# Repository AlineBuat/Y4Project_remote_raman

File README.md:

# Y4Project_remote_raman
Final Year MEng Biomedical Engineering Individual Project code

Created by Aline BUAT, 2021-2022

Project title "Detecting Bioweapons with Standoff Raman Spectroscopy"

These are code and files used during the project and used to generate the figures in the Final Report.

This repository contains the following folders:
- the code used to analyse data
- Arduino Control: arduino programs used to send positional data to the DACs, used to control Galvo Mirrors. Arduino programs to read data from a Quadrant photodiode, and translate it into positional information. program to Send and receive packets using NRF24L01 transceiver modules on Arduino Nano (transmitter) and Arduino Due (Receiver).
- EagleShield: Arduino Shield layout (schematic, board, project files) to control 2 galvo mirrors
- Raman: spectral data (.csv)  in folders. MATLAB programs to analyse the spectral data (plotRaman_20220601.m). requires the "BEADS" MATLAB package to run.
- BeamQuality: analyse images containing laser spots as imaged by a camera evaluated along a distance around the focal point, to find the spot size. Finally, plot spot size vs distance around the focal point to find M squared quality of the beam.

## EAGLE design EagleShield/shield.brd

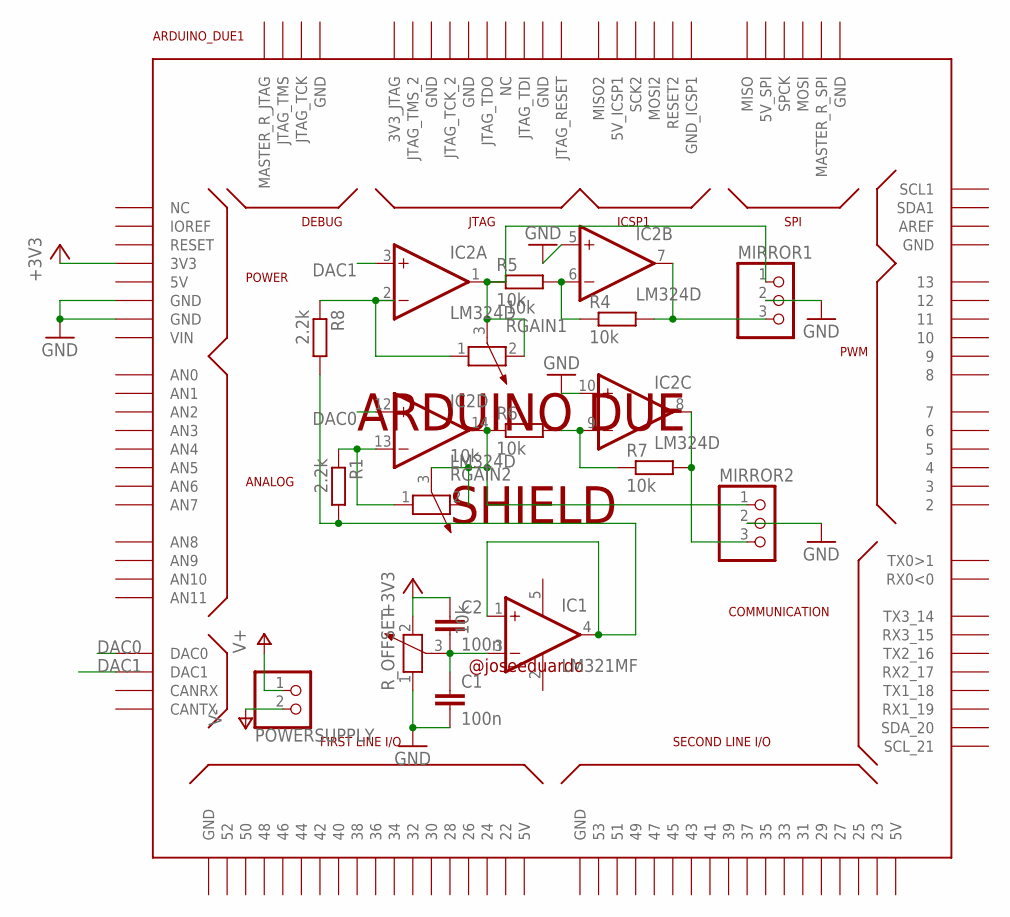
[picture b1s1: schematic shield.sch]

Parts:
ARDUINO_DUE1: ARDUINO_DUE_SHIELD
C1, C2: 100n; C0201
IC1: LM321MF; SOT23-5
IC2: LM324D; SO14
MIRROR1, MIRROR2: PINHD-1X3; 1X03
POWERSUPPLY: PINHD-1X2; 1X02
R1, R8: 2.2k; 0207/10
R4, R5, R6, R7: 10k; 0207/10
RGAIN1, RGAIN2: 10k; PT-10
R_OFFSET: 10k; PT-10

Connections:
+3V3: ARDUINO_DUE1.3V3, C2.1, R_OFFSET.2
DAC0: ARDUINO_DUE1.DAC0, IC2.12 (+IN)
DAC1: ARDUINO_DUE1.DAC1, IC2.3 (+IN)
GND: ARDUINO_DUE1.GND, ARDUINO_DUE1.GND_1 (GND), C1.2, IC2.5 (+IN), IC2.10 (+IN), MIRROR1.2, MIRROR2.2, R_OFFSET.1
unnamed: IC2.6 (-IN), R4.1, R5.2
unnamed: IC1.1 (+IN), IC1.4 (OUT), R1.2, R8.2
unnamed: IC2.9 (-IN), R6.2, R7.1
unnamed: IC2.1 (OUT), MIRROR1.1, R5.1, RGAIN1.2, RGAIN1.3
unnamed: IC2.2 (-IN), R8.1, RGAIN1.1
unnamed: IC2.14 (OUT), MIRROR2.1, R6.1, RGAIN2.2, RGAIN2.3
unnamed: IC2.8 (OUT), MIRROR2.3, R7.2
unnamed: IC2.13 (-IN), R1.1, RGAIN2.1
unnamed: IC2.7 (OUT), MIRROR1.3, R4.2
unnamed: C1.1, C2.2, IC1.3 (-IN), R_OFFSET.3
V+: IC1.5 (V+), IC2.4 (V+), POWERSUPPLY.1
V-: IC1.2 (V-), IC2.11 (V-), POWERSUPPLY.2

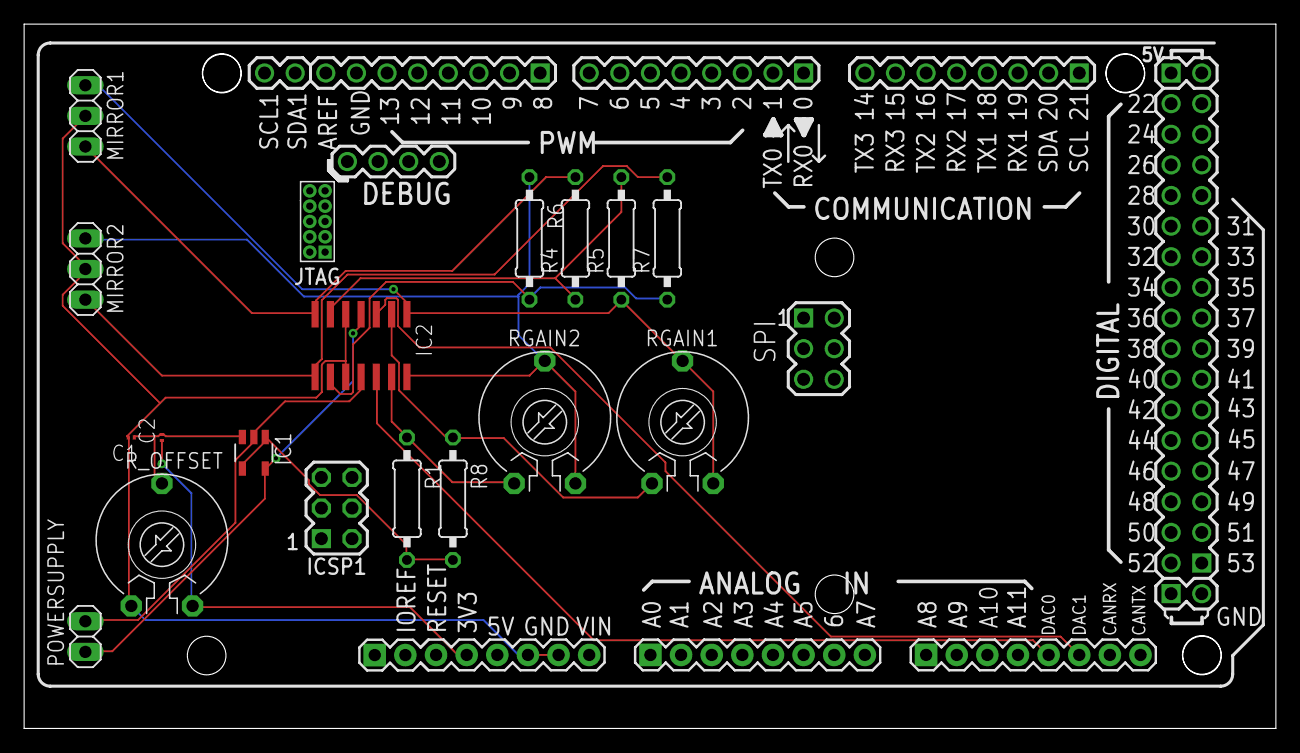
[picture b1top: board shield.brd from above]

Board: 2 copper layers, 103.8 x 58.4 mm, 17 parts (0 on the bottom side), 16 nets.

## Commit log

2022-06-11 Initial commit.
2022-06-11 Add files
2022-06-11 Renamed folder
